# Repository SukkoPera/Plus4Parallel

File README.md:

# Plus4Parallel
Plus4Parallel is an Open Hardware Parallel Port Adapter that plugs into the Commodore Plus/4 User Port, turning it into a DB-25 connector similar to that found on PCs.

## Summary
The +4 User Port can be converted to a standard PC parallel port to some extent. It should be at least compatible with printers of the era bearing a *Centronics* interface (such as the Commodore MPS 1230, MPS-1550C or Epson LX-80, for instance). You will need a Parallel to Centronics cable to connect one, but those should be easy to find even nowadays.

Only the 8-bit data port and the `/STROBE` and `/BUSY` signals are handled.

The board plugs in the User Port, which means that it can also be used on a C16 or C116 through [a User Port card](https://github.com/SukkoPera/16up).

## Notes
**THIS BOARD IS UNTESTED!!!**

There is an alternative parallel cable layout from Solder/Synergy, which is different and incompatible with this layout, I think. Unfortunately I cannot find any information on it, it would be great if someone could help documenting it.

## Releases
If you want to get this board produced, you are recommended to get [the latest release](https://github.com/SukkoPera/Plus4Parallel/releases) rather than the current git version, as the latter might be under development and is not guaranteed to be working.

Every release is accompanied by its Bill Of Materials (BOM) file and any relevant notes about it, which you are recommended to read carefully.

## License
The Plus4Parallel documentation, including the design itself, is copyright &copy; SukkoPera 2022 and is licensed under the [Creative Commons Attribution-NonCommercial-ShareAlike 4.0 International License](https://creativecommons.org/licenses/by-nc-sa/4.0/).

This documentation is distributed *as is* and WITHOUT ANY EXPRESS OR IMPLIED WARRANTIES whatsoever with respect to its functionality, operability or use, including, without limitation, any implied warranties OF MERCHANTABILITY, SATISFACTORY QUALITY, FITNESS FOR A PARTICULAR PURPOSE or infringement. We expressly disclaim any liability whatsoever for any direct, indirect, consequential, incidental or special damages, including, without limitation, lost revenues, lost profits, losses resulting from business interruption or loss of data, regardless of the form of action or legal theory under which the liability may be asserted, even if advised of the possibility or likelihood of such damages.

## Support the Project
If you want to get some boards manufactured, you can get them from PCBWay through this link:

You get my gratitude and cheap, professionally-made and good quality PCBs, I get some credit that will help with this and [other projects](https://www.pcbway.com/project/member/shareproject/?bmbid=41100). You won't even have to worry about the various PCB options, it's all pre-configured for you!

Also, if you still have to register, [you can use this link](https://www.pcbway.com/setinvite.aspx?inviteid=41100) to get some bonus initial credit (and yield me some more).

You can also buy me a coffee if you want:

## Thanks
* This is based on some old documents found with the Wayback Machine. They have been included in the [doc](doc/) directory.

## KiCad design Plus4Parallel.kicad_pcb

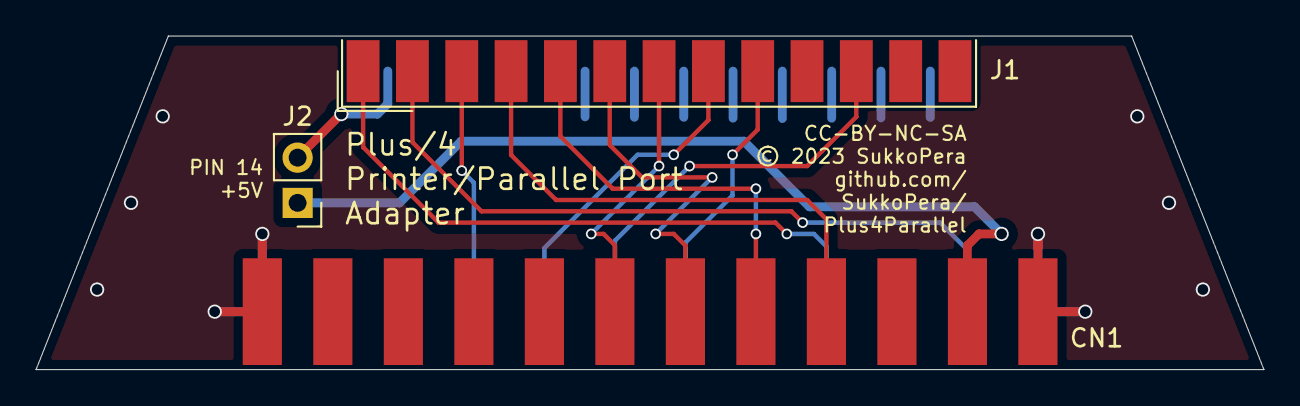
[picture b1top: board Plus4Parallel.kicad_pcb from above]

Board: 2 copper layers, 69.0 x 18.7 mm, 4 parts (1 on the bottom side), 13 nets.

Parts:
CN1: PLUS4_USERPORT; UserPortFemale
J1: DB25_Female_MountingHoles; DSUB-25_Female_EdgeMount_P2.77mm
J2: JMP_POWER; PinHeader_1x02_P2.54mm_Vertical
V0: LICENSE; cc_by_nc_sa

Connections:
+5V: CN1.2, J2.1
/busy: CN1.H, J1.11
/p0: CN1.B, J1.2
/p1: CN1.K, J1.3
/p2: CN1.4, J1.4
/p3: CN1.5, J1.5
/p4: CN1.6, J1.6
/p5: CN1.7, J1.7
/p6: CN1.J, J1.8
/p7: CN1.F, J1.9
/~strobe: CN1.D, J1.1
GND: CN1.1, CN1.12, CN1.A, CN1.N, J1.18, J1.19, J1.20, J1.21, J1.22, J1.23, J1.24, J1.25
unnamed: J1.14, J2.2

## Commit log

2023-03-05 Add power jumper Inspired by Amiga
2023-03-05 Work on simmetry Note that DB-25 footprint is still not centered, don't know why!
2023-04-07 +4 -> Plus/4
2023-04-07 Add renders and update README

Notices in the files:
Plus4Parallel.kicad_pcb:
Licensed under CC BY-NC-SA 4.0
© 2023 SukkoPera
